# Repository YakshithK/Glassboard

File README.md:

# Glassboard

A transparent NFC business card that lights up when you tap your phone to it. No battery. No charging. Ever.

---

## What is it

Glassboard is a credit card sized transparent circuit board. It stores my contact info and portfolio link using NFC. When someone taps their phone to it, two things happen at once: their phone opens my portfolio link, and three green LEDs on the card light up and animate.

The entire card runs off the energy from the phone's own NFC signal. There is no battery inside. Nothing to charge. The card just sits in your wallet and works whenever someone taps it.

Because it's built on a transparent substrate, you can see through the card. Every trace, every component, and the antenna spiral are all visible. It looks like a piece of glass with circuits inside.

---

## Why I made it

I kept handing people plain paper business cards at hackathons. It felt wrong. I build hardware, but the card said nothing about that.

I wanted a card that proved what I do the moment someone touched it. So I built one.

---

## How it works

The card has two chips on it.

The first is the **NT3H2111**, an NFC chip from NXP. It stores my URL in its memory and harvests power from the phone's NFC field. When a phone gets close, the chip outputs around 3V on its power pin, which powers everything else on the card.

The second is the **ATtiny202**, a tiny microcontroller. It spends almost all of its time asleep, drawing basically no power. When the NFC chip detects a phone, it sends a signal to the ATtiny, which wakes up instantly, runs the LED animation for about 2 seconds, then goes back to sleep.

The antenna is a copper spiral coil built directly into the circuit board. It has 5 turns and is tuned to 13.56 MHz, which is the frequency all NFC phones use.

The three LEDs are green because green LEDs turn on at a lower voltage than blue or white ones, which matters a lot when you're running off harvested power.

---

## How to use it

**Tapping it:**
Hold the card against the back of any NFC enabled phone (most smartphones made after 2015 have NFC). The phone will show a notification to open a link. Tap it. The LEDs on the card will also light up at the same time.

If nothing happens, try moving the card around slowly. The NFC antenna in phones is usually near the top or center of the back.

**Changing the URL:**
1. Download the NXP TagWriter app (free on both iOS and Android)
2. Open the app and select "Write"
3. Choose "Link" and type in the URL you want
4. Hold your phone to the card
5. Done. The old URL is replaced with the new one

No programmer needed for this. The NFC chip handles it wirelessly.

**Reprogramming the LED animation:**
1. Get a CH340 USB to UART adapter (about $3 on Amazon)
2. Connect it to the three small pads on the bottom edge of the card: VCC, GND, and UPDI
3. Install megaTinyCore in Arduino IDE (add this URL to board manager: `http://drazzy.com/package_drazzy.com_index.json`)
4. Select board: ATtiny202, clock: 5MHz internal, programmer: UPDI
5. Open `firmware/glassboard.ino` and upload

---

## PCB

| Spec | Value |
|------|-------|
| Substrate | Transparent FPC (PET) |
| Layers | 2 |
| Thickness | 0.2mm |
| Dimensions | 85.6 x 54mm (credit card size) |
| Surface finish | ENIG (gold) |
| Made by | JLCPCB |

---

## Parts list

Full BOM with purchase links is in `BOM.csv`.

| Part | Description | Quantity |
|------|-------------|----------|
| NT3H2111W0FTT | NFC chip, TSSOP8 | 1 |
| ATtiny202-SSF | Microcontroller, SOIC8 | 1 |
| Wurth 150040GS73240 | Green LED, 0402 | 3 |
| 220nF cap | Decoupling, 0402 | 1 |
| 100nF cap | RESET filter, 0402 | 1 |
| 39pF cap | Antenna tuning, 0402 | 1 |
| 10pF cap | Optional tuning, 0402 (DNP) | 1 |
| 10k resistor | Pull-ups, 0402 | 4 |
| 3.3k resistor | LED current limit, 0402 | 3 |
| 1k resistor | UPDI protection, 0402 | 1 |
| Transparent FPC PCB | From JLCPCB | 1 |

Total cost is around $32 for 5 boards including shipping.

---

## Firmware

The firmware file is at `firmware/glassboard.ino`.

It puts the ATtiny202 into deep sleep mode. When the NT3H2111 detects a phone, its FD pin goes LOW, which triggers a hardware interrupt on the ATtiny. The MCU wakes up, runs a chase animation across the three LEDs, then goes back to sleep. The whole active cycle takes about 2 seconds.

---

## Files

```
glassboard/
├── README.md
├── BOM.csv
├── firmware/
│   └── glassboard.ino
├── hardware/
│   ├── glassboard.kicad_pro
│   ├── glassboard.kicad_sch
│   ├── glassboard.kicad_pcb
│   └── gerbers/
├── Glassboard_Zine.pdf
└── images/
    ├── 3d_front.png
    ├── 3d_back.png
    ├── pcb.png
    ├── schematic.png
    └── zine.png
```

---

## Zine page

---

Made by Yakshith Kommineni, age 17, Brampton Ontario Canada

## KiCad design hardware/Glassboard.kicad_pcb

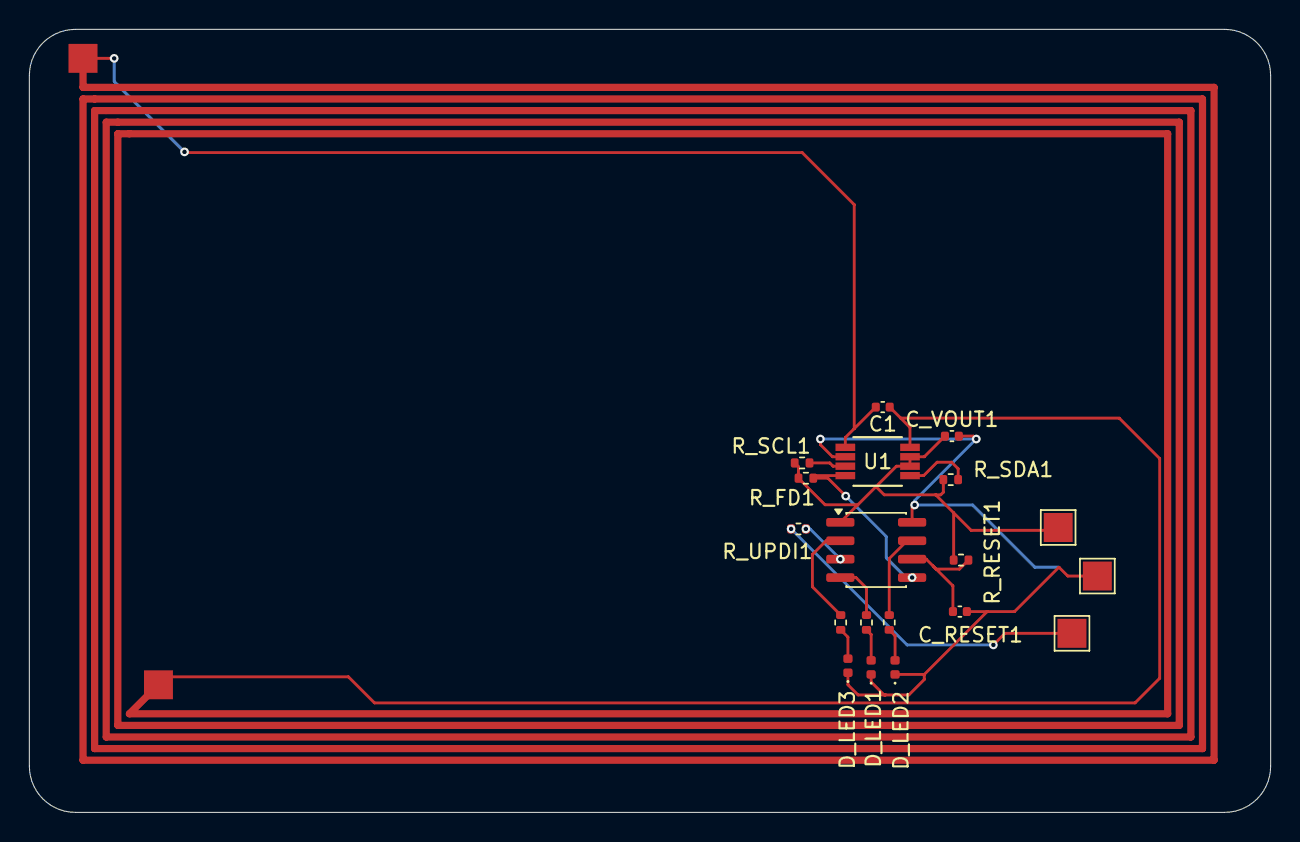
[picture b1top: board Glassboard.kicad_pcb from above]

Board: 2 copper layers, 85.6 x 54.0 mm, 17 parts (0 on the bottom side), 15 nets.

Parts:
C1: 39pF; C_0402_1005Metric
C_RESET1: 100nF; C_0402_1005Metric
C_VOUT1: 220nF; C_0402_1005Metric
D_LED1, D_LED2, D_LED3: GREEN 0402; LED_0402_1005Metric
L_ANTENNA_COIL1: 1.5uH; NFC_Credit_Card
R_FD1: 10K; R_0402_1005Metric
R_LED1, R_LED2, R_LED3: 3.3K; R_0402_1005Metric
R_RESET1: 10K; R_0402_1005Metric
R_SCL1: 10K; R_0402_1005Metric
R_SDA1: 10K; R_0402_1005Metric
R_UPDI1: 1K; R_0402_1005Metric
U1: TSSOP_1W0FTTJ_NXP; NT3H2111W0FTTJ
U2: ATtiny202-SS; SOIC-8_3.9x4.9mm_P1.27mm

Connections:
/FD: R_FD1.2, U1.4 (FD), U2.5 (PA2)
/SCL: R_SCL1.2, U1.3 (SCL)
/SDA: R_SDA1.2, U1.5 (SDA)
GND: C_RESET1.2, C_VOUT1.2, D_LED1.1 (K), D_LED2.1 (K), D_LED3.1 (K), U1.2 (VSS), U2.8 (GND)
unnamed: D_LED1.2 (A), R_LED1.2
unnamed: D_LED2.2 (A), R_LED2.2
unnamed: D_LED3.2 (A), R_LED3.2
unnamed: C1.2, L_ANTENNA_COIL1.1, U1.1 (LA)
unnamed: C1.1, L_ANTENNA_COIL1.2, U1.8 (LB)
unnamed: R_LED1.1, U2.4 (PA1)
unnamed: R_LED2.1, U2.7 (PA3)
unnamed: R_LED3.1, U2.2 (PA6)
unnamed: R_UPDI1.1, U2.3 (PA7)
unnamed: C_RESET1.1, R_RESET1.2, U2.6 (~RESET/PA0)
VOUT: C_VOUT1.1, R_FD1.1, R_RESET1.1, R_SCL1.1, R_SDA1.1, U1.6 (VCC), U1.7 (VOUT), U2.1 (VCC)

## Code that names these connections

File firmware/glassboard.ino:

/*
 * Glassboard — NFC Business Card Firmware
 * ATtiny202 / megaTinyCore
 * 
 * Behavior:
 *   - Deep sleep at ~0.1uA drawing essentially nothing
 *   - NT3H2111 FD pin goes LOW when phone NFC field detected
 *   - PA2 interrupt wakes MCU instantly
 *   - Runs LED animation sequence (~2 seconds)
 *   - Goes back to sleep
 * 
 * Pin assignments:
 *   PA2 - FD input from NT3H2111 (interrupt, active LOW)
 *   PA1 - LED1
 *   PA3 - LED2
 *   PA6 - LED3
 *   PA7 - UPDI (programming, do not use)
 *   PA0 - RESET (do not use)
 */

#include <avr/sleep.h>
#include <avr/interrupt.h>

#define LED1 PIN_PA1
#define LED2 PIN_PA3
#define LED3 PIN_PA6
#define FD_PIN PIN_PA2

// animation timing ms
#define STEP_DELAY 80
#define PULSE_DELAY 40

void allOff() {
  digitalWrite(LED1, LOW);
  digitalWrite(LED2, LOW);
  digitalWrite(LED3, LOW);
}

void allOn() {
  digitalWrite(LED1, HIGH);
  digitalWrite(LED2, HIGH);
  digitalWrite(LED3, HIGH);
}

// chase: 1 -> 2 -> 3 -> all -> off, repeat
void runAnimation() {
  // chase forward
  for (int i = 0; i < 3; i++) {
    digitalWrite(LED1, HIGH); delay(STEP_DELAY);
    digitalWrite(LED1, LOW);
    digitalWrite(LED2, HIGH); delay(STEP_DELAY);
    digitalWrite(LED2, LOW);
    digitalWrite(LED3, HIGH); delay(STEP_DELAY);
    digitalWrite(LED3, LOW);
  }

  // all flash 3x
  for (int i = 0; i < 3; i++) {
    allOn();  delay(PULSE_DELAY * 2);
    allOff(); delay(PULSE_DELAY);
  }

  // slow fade out (PWM approximation via toggling)
  for (int brightness = 10; brightness > 0; brightness--) {
    allOn();  delay(brightness * 3);
    allOff(); delay((10 - brightness) * 3);
  }

  allOff();
}

// interrupt service routine — just wakes MCU, no action needed
ISR(PORTA_PORT_vect) {
  // clear the interrupt flag for PA2
  PORTA.INTFLAGS = PIN2_bm;
}

void goToSleep() {
  // configure PA2 as input with pullup, trigger on falling edge (FD goes LOW)
  pinMode(FD_PIN, INPUT_PULLUP);
  PORTA.PIN2CTRL = PORT_PULLUPEN_bm | PORT_ISC_FALLING_gc;

  set_sleep_mode(SLEEP_MODE_PWR_DOWN);
  sleep_enable();
  sei();
  sleep_cpu();       // MCU stops here until interrupt
  sleep_disable();
  cli();
}

void setup() {
  pinMode(LED1, OUTPUT);
  pinMode(LED2, OUTPUT);
  pinMode(LED3, OUTPUT);
  allOff();

  // brief startup flash so you know it programmed correctly
  allOn(); delay(100); allOff();
}

void loop() {
  goToSleep();       // sleep until phone tap
  runAnimation();    // phone tapped — animate
  // loop: go back to sleep
}

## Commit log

2026-05-23 added zine and references in readme
2026-05-23 Fix image links in README.md
    Updated image file names in README.md to use underscores.
2026-05-23 remove duplicate kicad files
2026-05-23 Refine README content for clarity and consistency
    Updated text for clarity and formatting in README.
2026-05-23 Update BOM with new components and pricing
    Updated component details including manufacturers and links, and adjusted quantities and costs.
2026-05-23 Update BOM.csv with new components and details
2026-05-23 Modify capacitor entries in BOM.csv
    Updated the BOM to replace C3 and C4 with C2 and C3, respectively.
2026-05-23 fixed schematic names
2026-05-29 Include total cost in BOM.csv
    Added total cost calculation for BOM.
